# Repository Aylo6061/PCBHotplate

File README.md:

# PCBHotplate
A USB C powered PCB-based hotplate, with separable heater elements.

There are several PCB-project directories, HPcontroller contains the controller, while HPheater contains the heater.

# Inputs and Indicators
D_PD_POW indicates PD power is on
D_3v3_POW indicated 3v3 power is on
D_HOT indicates the plate is hot! dont touch!
D_HB is dicates that data is being sent or received on the serial port
D_MODE indicates the program mode is ON
D_RUN indicates the program or heater is running
D_HEAT indicates the heater is on
D_RTD indicates the RTD protection is tripped

# Bom (rough)

flyback diode - at least 25V Vr, capable of ~5A average current (overkill).  STR8100LBF would work.
capacitor- at least 25-30V probably like 100uF?  depends on switching frequency.
fet driver NCP81071B
Fet AOSD32334C dual nfet
non inverting buffer SN74HCS125PWR

# TODO

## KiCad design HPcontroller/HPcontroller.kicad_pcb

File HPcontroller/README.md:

# README

some future stuff will go here

# BUGS

pin 1 and 3 are swapped on U3, which makes the thermisor protection circuit not work.  I cut R9 jumper to fix "fix" this, at some point I'll verify that it works by bodge wiring.

GPIO 9 is routed to the MODE switch, however GPIO 9 is also the boot strapping pin to force the bootloader to turn on- therefore it must be switched to PROG when the code is programmed/when the micro boots.

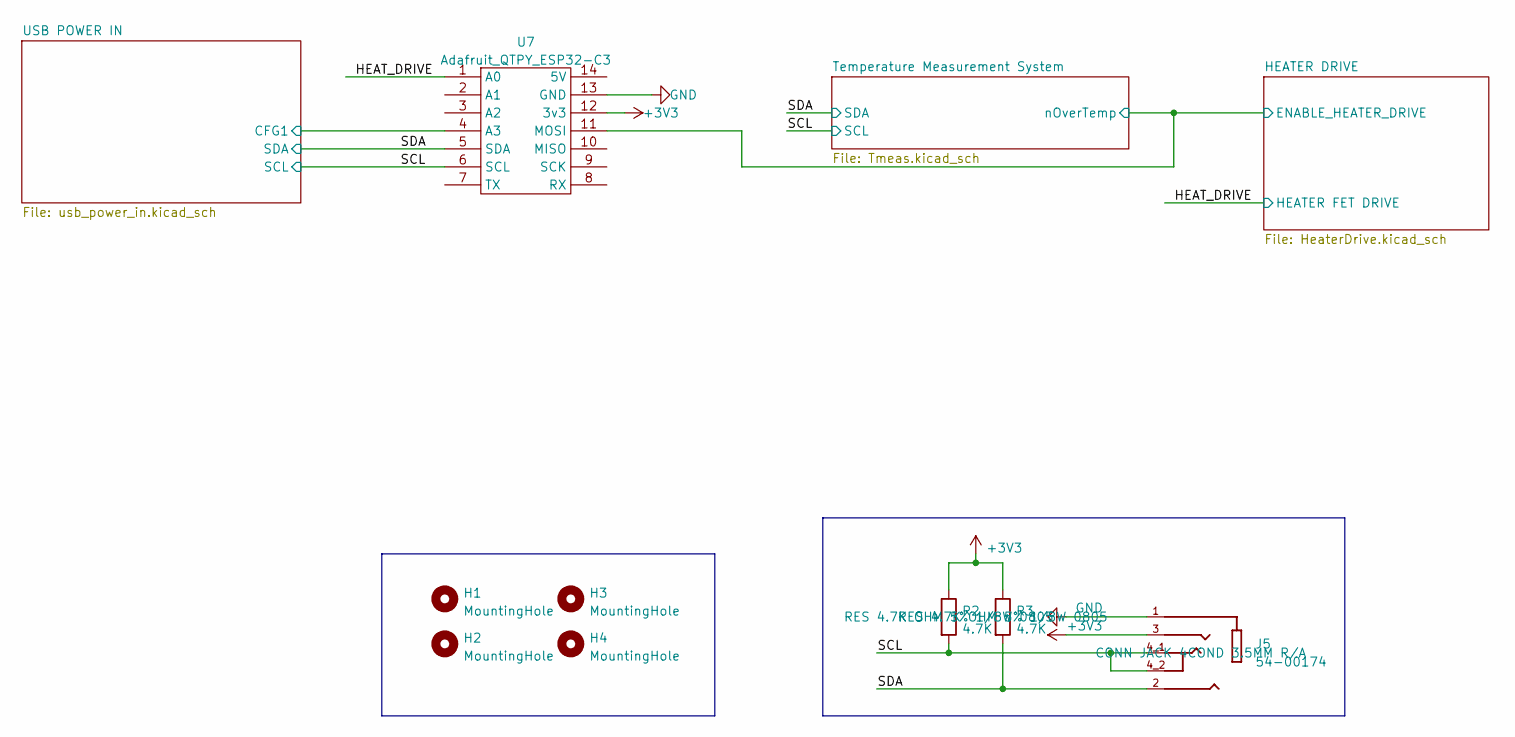
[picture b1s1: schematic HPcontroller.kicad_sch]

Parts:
H1, H2, H3, H4: MountingHole; MountingHole_2.7mm_M2.5
J5: 54-00174; TENSILITY_54-00174; PARTREV A; Digikey PN 839-54-00174CT-ND
R2, R3: 4.7K; R_0805_2012Metric_Pad1.20x1.40mm_HandSolder; MPN RC0805JR-074K7L; Digikey PN 311-4.7KARCT-ND
U7: Adafruit_QTPY_ESP32-C3; XIAO-ESP32C3-SMD-cutout

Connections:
+3V3: J5.3, R2.1, R3.1, U7.12 (3v3); also elsewhere on the board
/HEATER DRIVE/ENABLE_HEATER_DRIVE: U7.11 (MOSI); also elsewhere on the board
/HEAT_DRIVE: U7.1 (A0); also elsewhere on the board
/SCL: J5.4_1, J5.4_2, R2.2, U7.6 (SCL); also elsewhere on the board
/SDA: J5.2, R3.2, U7.5 (SDA); also elsewhere on the board
/USB POWER IN/CFG1: U7.4 (A3); also elsewhere on the board
GND: J5.1, U7.13 (GND); also elsewhere on the board

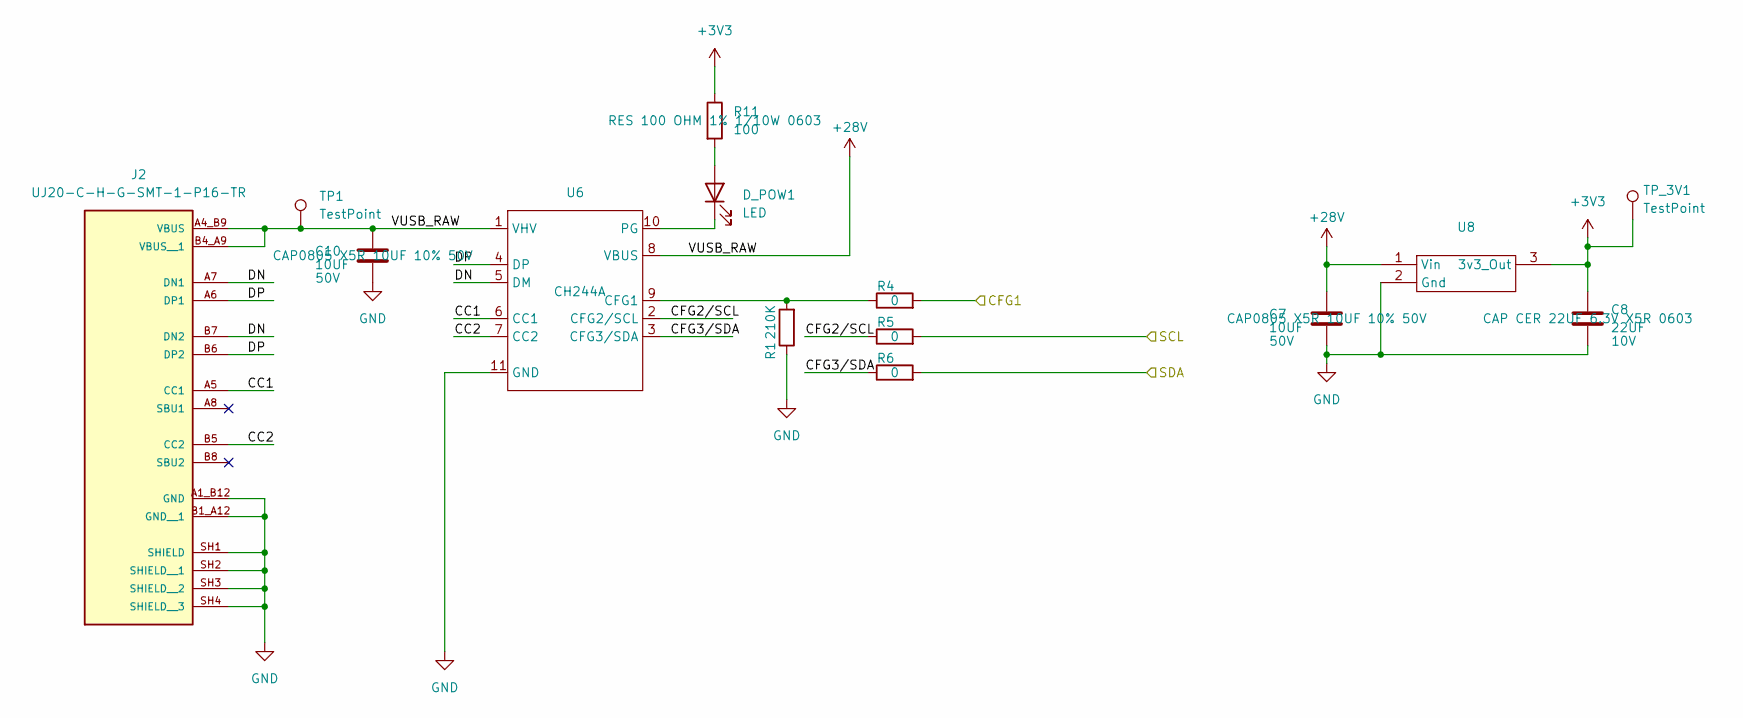
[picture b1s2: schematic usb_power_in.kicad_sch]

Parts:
C7, C10: 10UF; C_0805_2012Metric; Voltage 50V; MPN GMC21X5R106K50NT; Digikey PN 490-18663-1-ND
C8: 22UF; C_0603_1608Metric; Voltage 10V; MPN CL10A226MQ8NRNE; Digikey PN CL10A226MP8NUNE
D_POW1: LED; LED_0603_1608Metric_Pad1.05x0.95mm_HandSolder
J2: UJ20-C-H-G-SMT-1-P16-TR; SAMESKY_UJ20-C-H-G-SMT-1-P16-TR; PARTREV 1.0
R1: 210K; R_0603_1608Metric; MPN RMCF0603FT210K
R4, R5, R6: 0; R_0805_2012Metric_Pad1.20x1.40mm_HandSolder; MPN RMCF0805ZT0R00
R11: 100; R_0603_1608Metric; MPN RMCF0603FT100R; Digikey PN A130128CT-ND
TP1: TestPoint; TestPoint_Pad_D1.5mm
TP_3V1: TestPoint; TestPoint_Pad_D1.5mm
U6: CH244A; SSOP-10-1EP_3.9x4.9mm_P1mm_EP2.1x3.3mm
U8: D78B33-0.5; MPN D78B33-0.5

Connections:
+3V3: C8.1, R11.1, TP_3V1.1 (1_1), U8.3 (3v3_Out); also elsewhere on the board
+28V: C7.1, C10.1, J2.A4_B9 (VBUS), J2.B4_A9 (VBUS__1), TP1.1 (1_1), U6.1 (VHV), U6.8 (VBUS), U8.1 (Vin); also elsewhere on the board
/SCL: R5.2; also elsewhere on the board
/SDA: R6.2; also elsewhere on the board
/USB POWER IN/CC1: J2.A5 (CC1), U6.6 (CC1)
/USB POWER IN/CC2: J2.B5 (CC2), U6.7 (CC2)
/USB POWER IN/CFG1: R4.2; also elsewhere on the board
/USB POWER IN/CFG2/SCL: R5.1, U6.2 (CFG2/SCL)
/USB POWER IN/CFG3/SDA: R6.1, U6.3 (CFG3/SDA)
/USB POWER IN/DN: J2.A7 (DN1), J2.B7 (DN2), U6.5 (DM)
/USB POWER IN/DP: J2.A6 (DP1), J2.B6 (DP2), U6.4 (DP)
GND: C7.2, C8.2, C10.2, J2.A1_B12 (GND), J2.B1_A12 (GND__1), J2.SH1 (SHIELD), J2.SH2 (SHIELD__1), J2.SH3 (SHIELD__2), J2.SH4 (SHIELD__3), R1.1, U6.11 (GND), U8.2 (Gnd); also elsewhere on the board
unnamed: D_POW1.2 (A), R11.2
unnamed: D_POW1.1 (K), U6.10 (PG)
unnamed: R1.2, R4.1, U6.9 (CFG1)

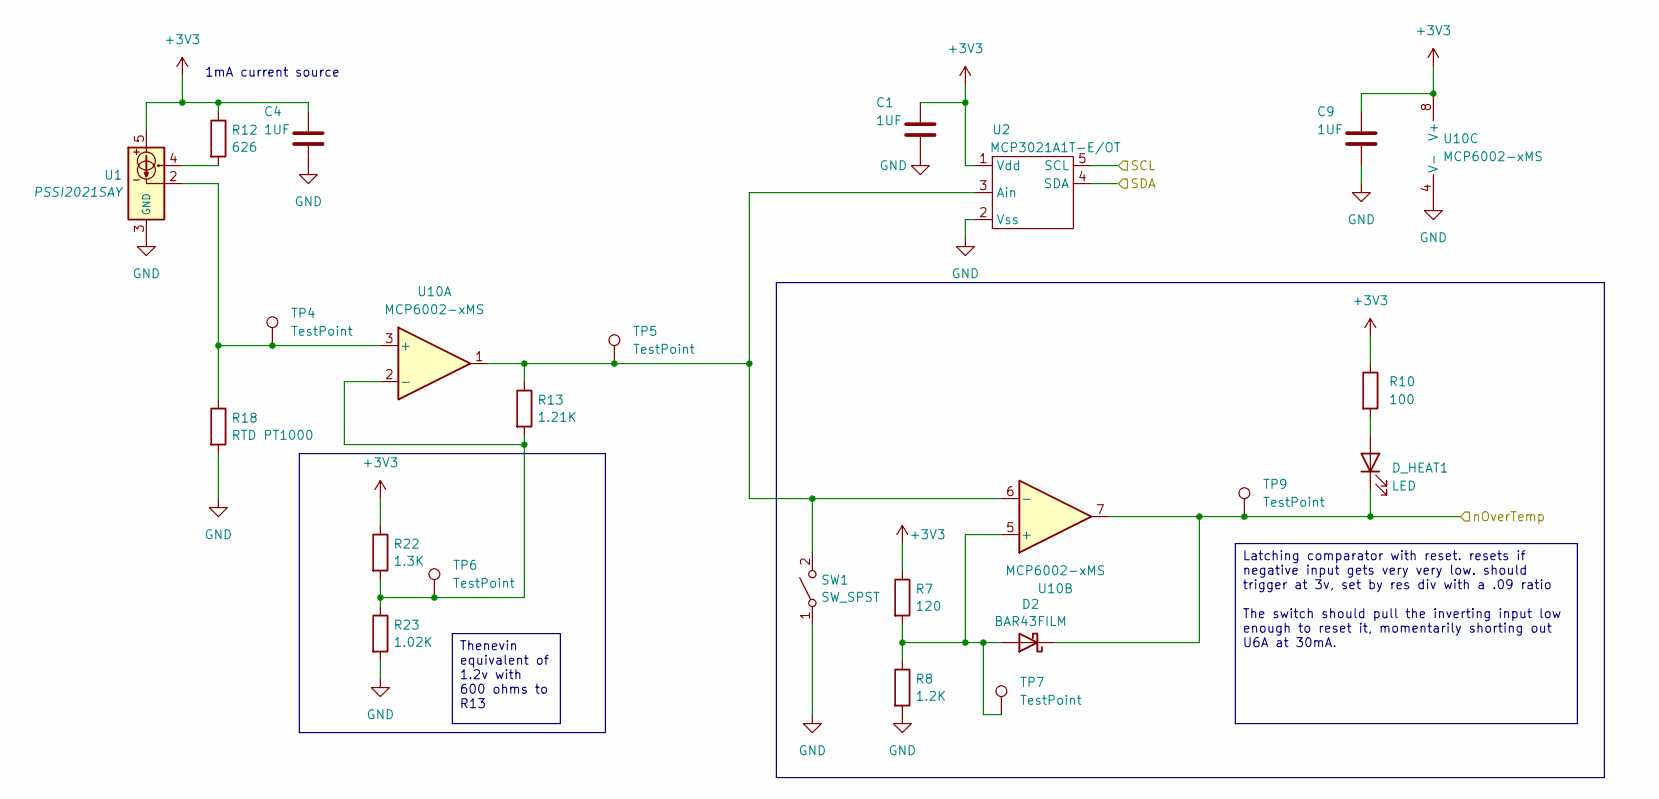
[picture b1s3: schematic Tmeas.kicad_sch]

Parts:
C1, C4, C9: 1UF; C_0805_2012Metric; MPN GRM219R7YA105KA12D; Digikey PN 1276-1066-1-ND
D2: BAR43FILM; SOT-23; MPN BAR43FILM
D_HEAT1: LED; LED_0603_1608Metric_Pad1.05x0.95mm_HandSolder
R7: 120; R_0603_1608Metric; MPN ERJ-3EKF1200V
R8: 1.2K; R_0603_1608Metric; MPN CR0603-FX-1201ELF
R10: 100; R_0603_1608Metric; MPN RMCF0603FT100R; Digikey PN A130128CT-ND
R12: 626; R_0603_1608Metric; MPN RT0603BRD07626RL
R13: 1.21K; R_0603_1608Metric; MPN RC0603FR-071K21L
R18: RTD PT1000; R_0805_2012Metric; MPN 30200145
R22: 1.3K; R_0603_1608Metric; MPN RMCF0603FT1K30
R23: 1.02K; R_0603_1608Metric; MPN ERJ-3EKF1021V
SW1: SW_SPST; SW_EVQ-P7J01P; MPN EVQ-P7J01P
TP4, TP5, TP6, TP7, TP9: TestPoint; TestPoint_Pad_D1.5mm
U1: PSSI2021SAY; SOT-353_SC-70-5; MPN PSSI2021SAY
U2: MCP3021A1T-E/OT; SOT-23-5; MPN MCP3021A1T-E/OT; Digikey PN MCP3021A1T-E/OTCT-ND
U10: MCP6002-xMS; SOIC-8_3.9x4.9mm_P1.27mm; MPN MCP6002T-E/SN

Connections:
+3V3: C1.1, C4.1, C9.1, R7.1, R10.1, R12.1, R22.1, U1.5, U2.1 (Vdd), U10.8 (V+); also elsewhere on the board
/HEATER DRIVE/ENABLE_HEATER_DRIVE: D2.3 (K), D_HEAT1.1 (K), TP9.1 (1_1), U10.7; also elsewhere on the board
/SCL: U2.5 (SCL); also elsewhere on the board
/SDA: U2.4 (SDA); also elsewhere on the board
GND: C1.2, C4.2, C9.2, R8.2, R18.2, R23.2, SW1.1 (A), U1.3 (GND_3), U2.2 (Vss), U10.4 (V-); also elsewhere on the board
unnamed: D2.1 (A), R7.2, R8.1, TP7.1 (1_1), U10.5 (+)
unnamed: D_HEAT1.2 (A), R10.2
unnamed: R12.2, U1.4
unnamed: R13.1, SW1.2 (B), TP5.1 (1_1), U2.3 (Ain), U10.1, U10.6 (-)
unnamed: R18.1, TP4.1 (1_1), U1.2, U10.3 (+)
unnamed: R13.2, R22.2, R23.1, TP6.1 (1_1), U10.2 (-)

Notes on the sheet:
1mA current source
Thenevin equivalent of 1.2v with 600 ohms to R13
Latching comparator with reset. resets if negative input gets very very low. should trigger at 3v, set by res div with a .09 ratio The switch should pull the inverting input low enough to reset it, momentarily shorting out U6A at 30mA.

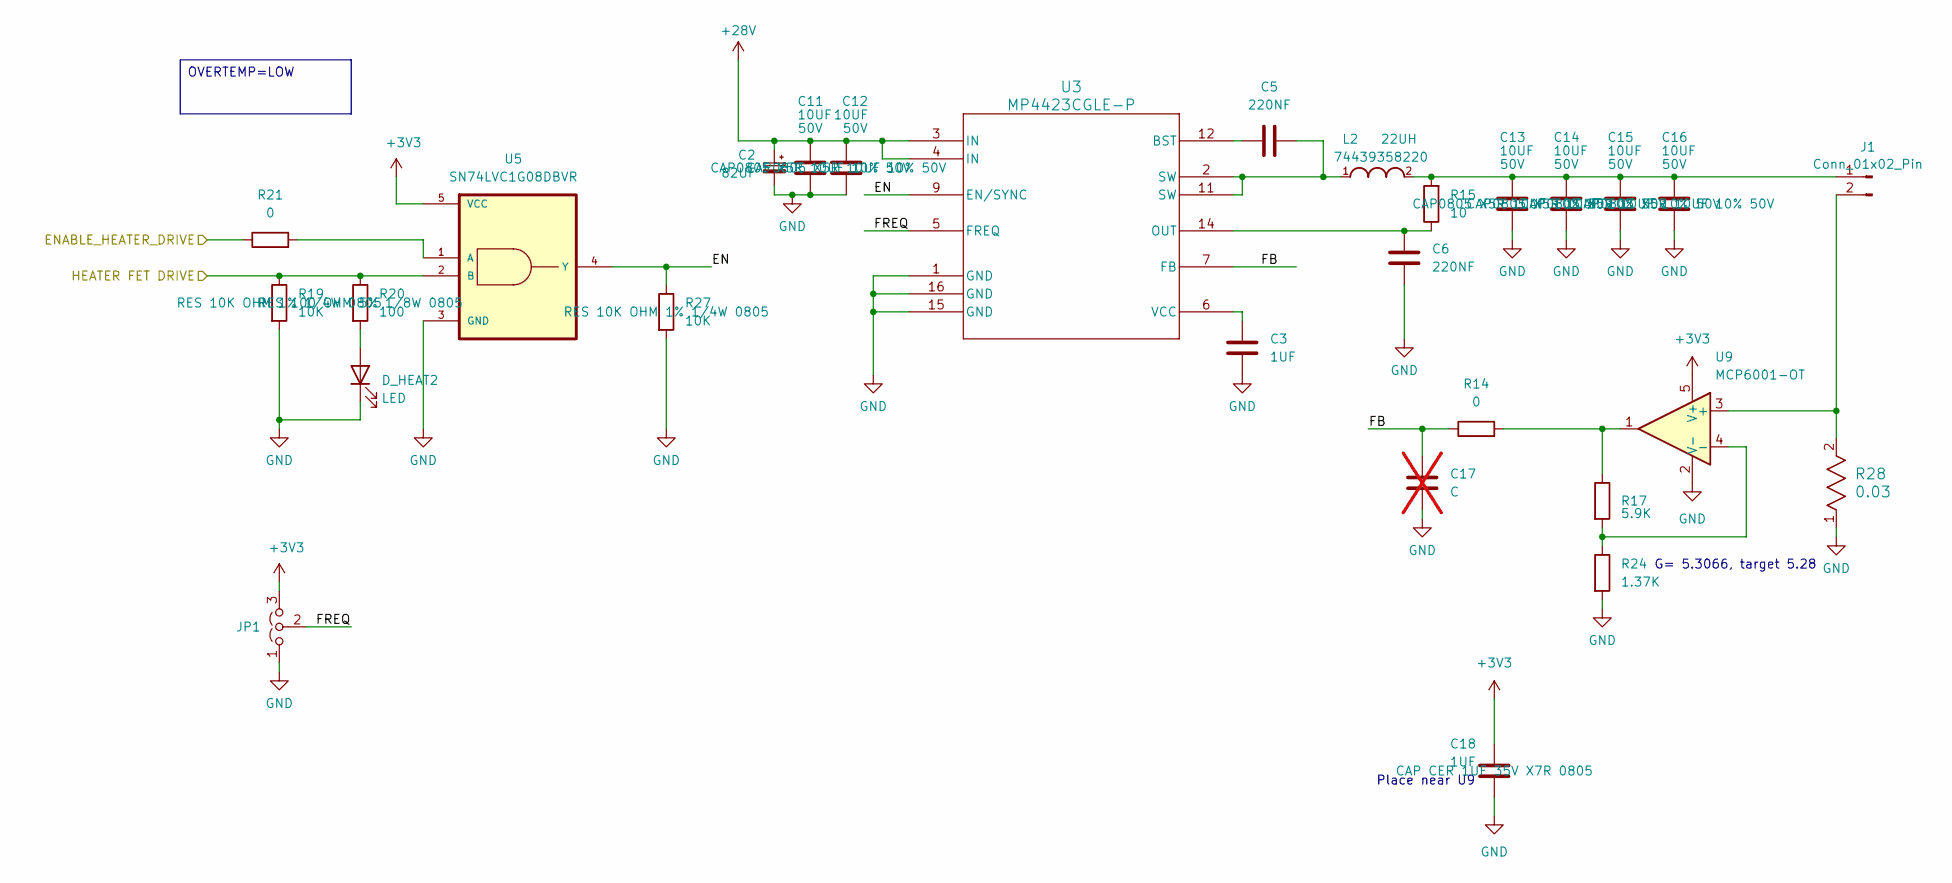
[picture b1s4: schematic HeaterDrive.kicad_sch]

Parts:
C2: 82UF; CP_Elec_8x6.7; MPN A768KE826M1VLAE036
C3: 1UF; C_0603_1608Metric; MPN CL10B105MO8NNWC
C5, C6: 220NF; C_0603_1608Metric; MPN CL10E224KA84PNC
C11, C12, C13, C14, C15, C16: 10UF; C_0805_2012Metric; Voltage 50V; MPN GMC21X5R106K50NT; Digikey PN 490-18663-1-ND
C17: C; C_0603_1608Metric; not fitted
C18: 1UF; C_0805_2012Metric; MPN GRM219R7YA105KA12D; Digikey PN 1276-1066-1-ND
D_HEAT2: LED; LED_0603_1608Metric_Pad1.05x0.95mm_HandSolder
J1: Conn_01x02_Pin; S7051-42R_array
JP1: Jumper_3_Open; SolderJumper-3_P1.3mm_Open_RoundedPad1.0x1.5mm
L2: 22UH; WE-XHMI_8080; MPN 74439358220
R14: 0; R_0805_2012Metric_Pad1.20x1.40mm_HandSolder; MPN RMCF0805ZT0R00
R15: 10; R_0805_2012Metric_Pad1.20x1.40mm_HandSolder; MPN RMCF0805FT10R0
R17: 5.9K; R_0805_2012Metric_Pad1.20x1.40mm_HandSolder; MPN RMCF0805FT5K90
R19, R27: 10K; R_0805_2012Metric_Pad1.20x1.40mm_HandSolder; MPN RNCP0805FTD10K0; Digikey PN RNCP0805FTD10K0CT-ND
R20: 100; R_0805_2012Metric_Pad1.20x1.40mm_HandSolder; MPN CRGCQ0805J100R; Digikey PN A130128CT-ND
R21: 0; SolderJumper-2_P1.3mm_Bridged_RoundedPad1.0x1.5mm
R24: 1.37K; R_0805_2012Metric_Pad1.20x1.40mm_HandSolder; MPN MCR10ERTF1371
R28: 0.03; STA_CSSH2728_STP; MPN CSSH2728FT30L0
U3: MP4423CGLE-P; QFN-16_MPQ4423C_MNP; MPN MP4423CGLE-P
U5: SN74LVC1G08DBVR; SOT95P280X145-5N; MPN SN74LVC1G08DBVR
U9: MCP6001-OT; SOT-23-5; MPN MCP6001T-E/OT

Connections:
+3V3: C18.1, JP1.3 (B), U5.5 (VCC), U9.5 (V+); also elsewhere on the board
+28V: C2.1, C11.1, C12.1, U3.3 (IN), U3.4 (IN); also elsewhere on the board
/HEATER DRIVE/EN: R27.1, U3.9 (EN/SYNC), U5.4 (Y)
/HEATER DRIVE/ENABLE_HEATER_DRIVE: R21.1; also elsewhere on the board
/HEATER DRIVE/FB: C17.1, R14.1, U3.7 (FB)
/HEATER DRIVE/FREQ: JP1.2 (C), U3.5 (FREQ)
/HEAT_DRIVE: R19.1, R20.1, U5.2 (B); also elsewhere on the board
GND: C2.2, C3.2, C6.1, C11.2, C12.2, C13.2, C14.2, C15.2, C16.2, C17.2, C18.2, D_HEAT2.1 (K), JP1.1 (A), R19.2, R24.2, R27.2, R28.1, U3.1 (GND), U3.15 (GND), U3.16 (GND), U5.3 (GND), U9.2 (V-); also elsewhere on the board
unnamed: C5.2, L2.1, U3.2 (SW), U3.11 (SW)
unnamed: D_HEAT2.2 (A), R20.2
unnamed: C13.1, C14.1, C15.1, C16.1, J1.1, L2.2, R15.2
unnamed: J1.2, R28.2, U9.3 (+)
unnamed: R14.2, R17.1, U9.1
unnamed: C5.1, U3.12 (BST)
unnamed: C6.2, R15.1, U3.14 (OUT)
unnamed: C3.1, U3.6 (VCC)
unnamed: R21.2, U5.1 (A)
unnamed: R17.2, R24.1, U9.4 (-)

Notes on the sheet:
Place near U9
G= 5.3066, target 5.28
OVERTEMP=LOW

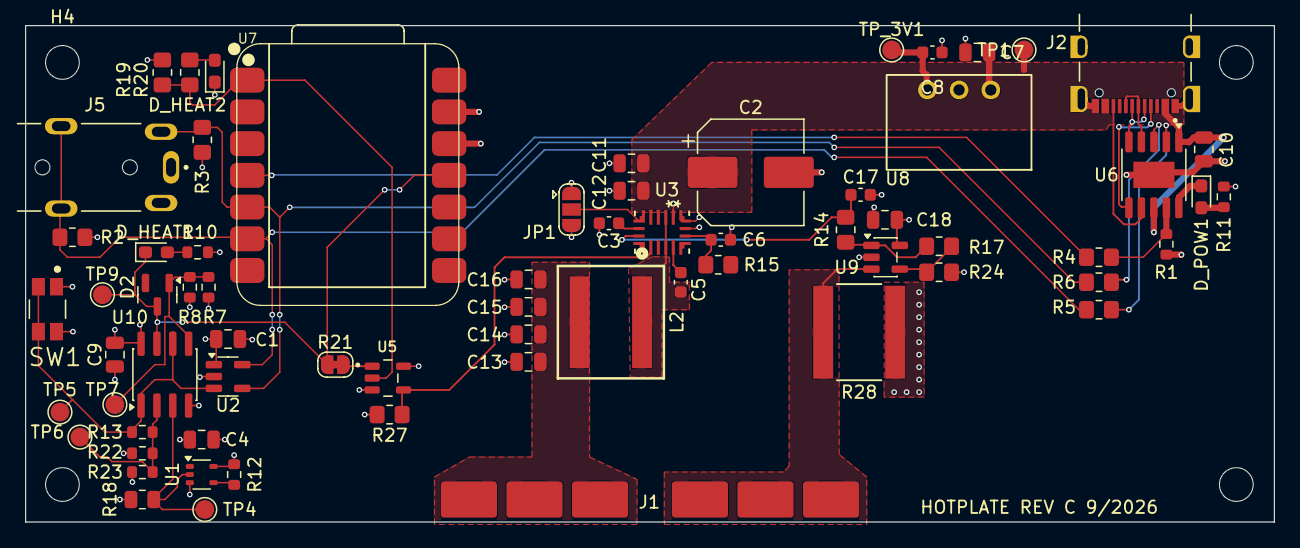
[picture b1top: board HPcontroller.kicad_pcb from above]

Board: 4 copper layers, 100.0 x 39.8 mm, 72 parts (0 on the bottom side), 36 nets.

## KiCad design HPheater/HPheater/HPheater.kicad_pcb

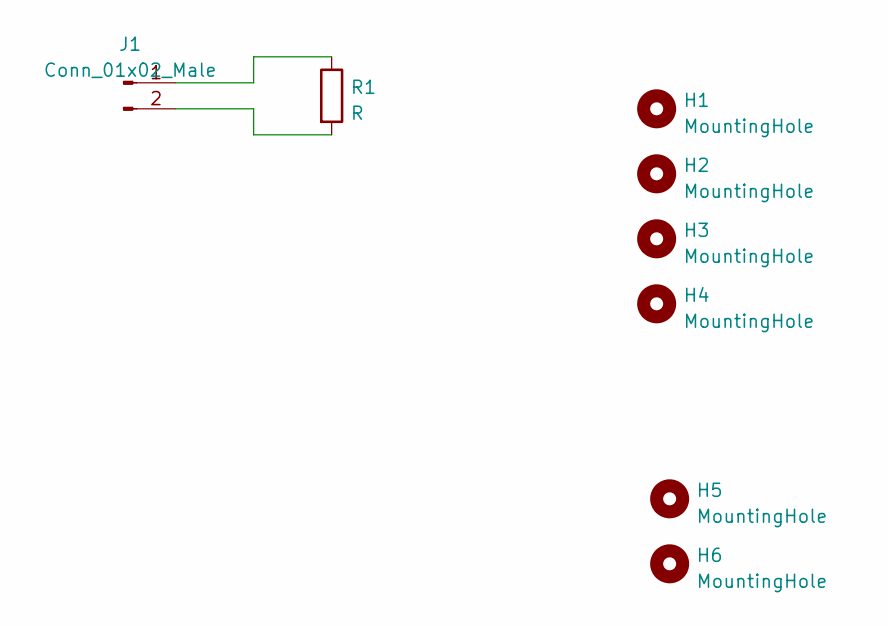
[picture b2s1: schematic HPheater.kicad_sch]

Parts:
H1, H2, H3, H4: MountingHole; MountingHole_2.5mm
H5, H6: MountingHole; MountingHole_2.7mm_M2.5
J1: Conn_01x02_Male; HEATER_CONTACT
R1: R; Heater_3ohm

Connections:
unnamed: J1.1, R1.1
unnamed: J1.2, R1.2

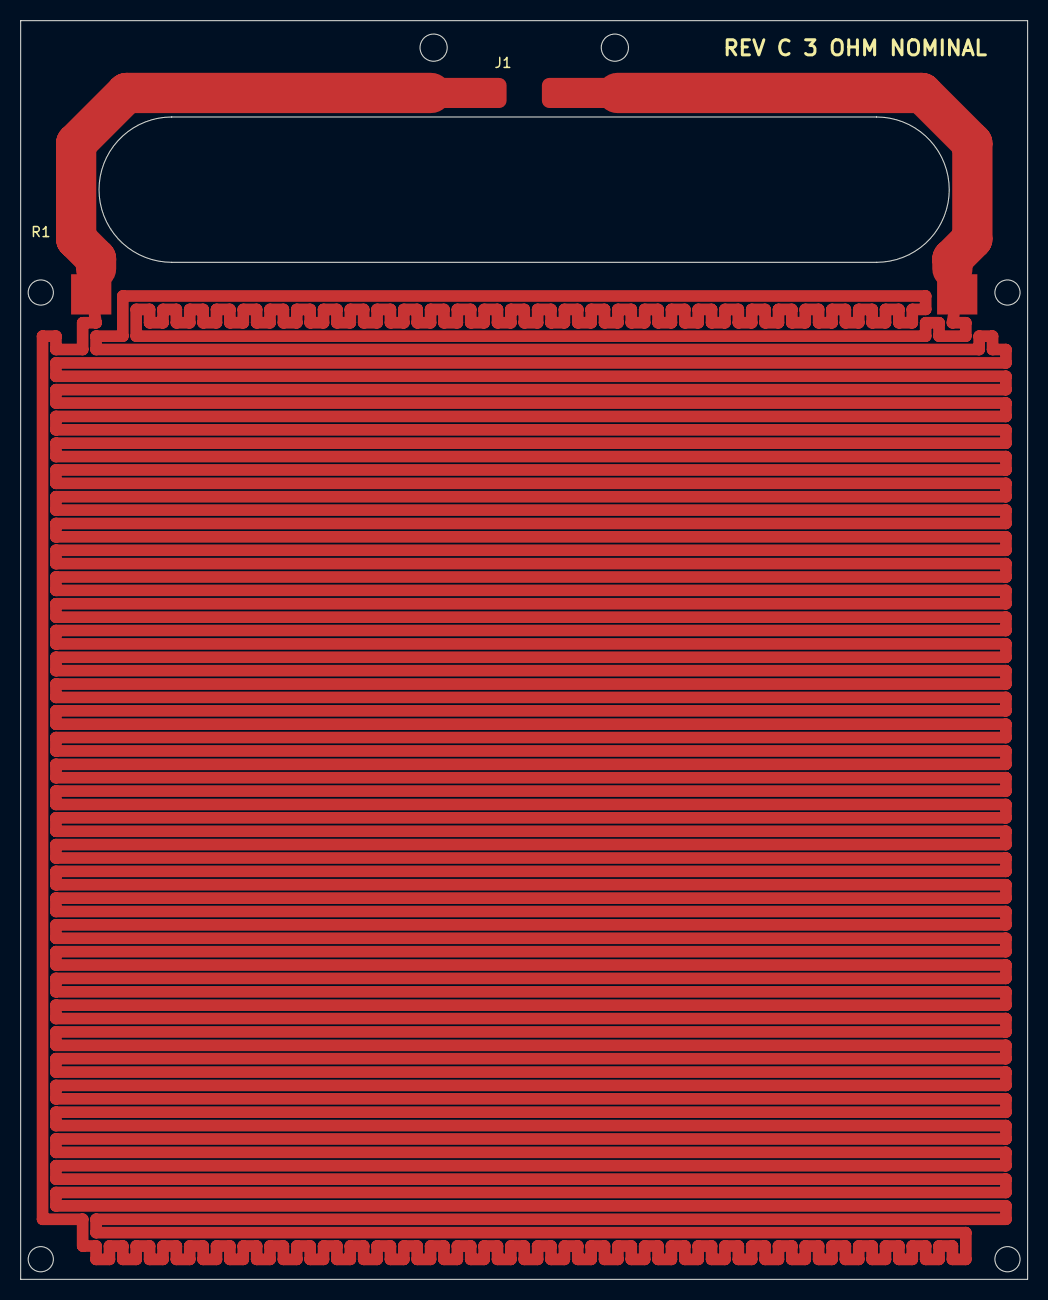
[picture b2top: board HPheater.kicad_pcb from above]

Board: 2 copper layers, 100.0 x 125.0 mm, 8 parts (0 on the bottom side), 2 nets.

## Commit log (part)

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2022-11-30 more design is done
2022-11-30 saved more changes
2022-12-01 assigned footprints, added some stuff to readme
2022-12-02 started layout
2022-12-02 routing more. waitingfor PD trigger to arrive
2022-12-15 minor pcb change to give TC wires more room
2022-12-15 started work on heater
2022-12-15 added scripts to design and draw heater
2022-12-15 started heater layout. need to make heater smaller to accomodate some kind of mounting holes, need to add mounting for controller
2022-12-15 fixed minor issues, added mounting
2022-12-15 changed heater size, added mounting, refined slot
2022-12-15 changed desired dimensions in plot design
2022-12-15 final tweaks/drc to HPheater. DO NOT repour zones, as there is a purposeful short
2022-12-15 added upllup to thermal protection circuit
2022-12-26 starting hotplate fw
2023-09-18 started revision
2023-09-18 added gititgnore
2023-09-19 design "finished" need to do bom and footprints and layout
2023-09-19 started routing, finished footprintns
2023-09-19 finished routing, moving on to heater
2023-09-20 added some comments and fixed readme link
2023-09-20 finished routing heater
2023-09-20 worked on bom, orderables from dk are in
2023-10-17 fixed C and R silk swap
2023-10-25 final fw
2023-10-25 calibration fw
2023-10-25 calibration notebook (jupyter)
2025-08-07 v3 routing
2025-09-25 new temp circuit
2025-10-01 finished temp meas stuff, laying out
2025-10-10 routing
2025-12-30 uploading routing
2026-05-12 fixed open on heater
2026-05-12 new gerbers
